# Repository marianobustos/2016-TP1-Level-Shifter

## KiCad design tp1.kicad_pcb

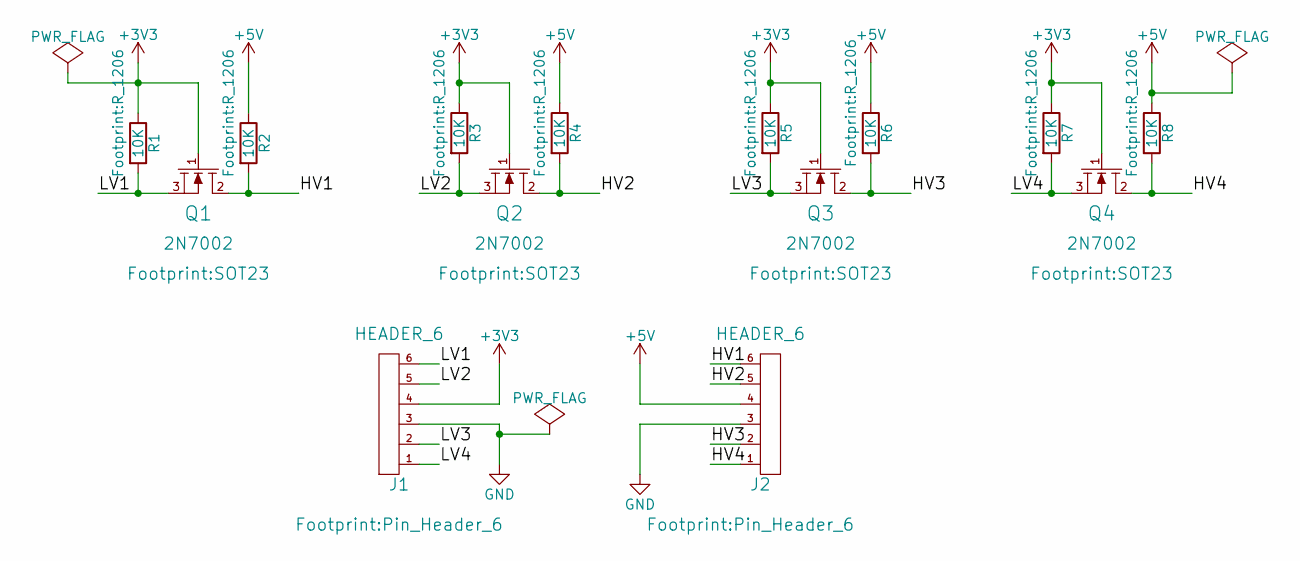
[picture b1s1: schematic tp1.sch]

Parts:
J1, J2: HEADER_6; Pin_Header_6
Q1, Q2, Q3, Q4: 2N7002; SOT23
R1, R2, R3, R4, R5, R6, R7, R8: 10K; R_1206

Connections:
+3V3: J1.4, Q1.1 (G), Q2.1 (G), Q3.1 (G), Q4.1 (G), R1.1, R3.1, R5.1, R7.1
+5V: J2.4, R2.1, R4.1, R6.1, R8.1
/HV1: J2.6, Q1.2 (D), R2.2
/HV2: J2.5, Q2.2 (D), R4.2
/HV3: J2.2, Q3.2 (D), R6.2
/HV4: J2.1, Q4.2 (D), R8.2
/LV1: J1.6, Q1.3 (S), R1.2
/LV2: J1.5, Q2.3 (S), R3.2
/LV3: J1.2, Q3.3 (S), R5.2
/LV4: J1.1, Q4.3 (S), R7.2
GND: J1.3, J2.3

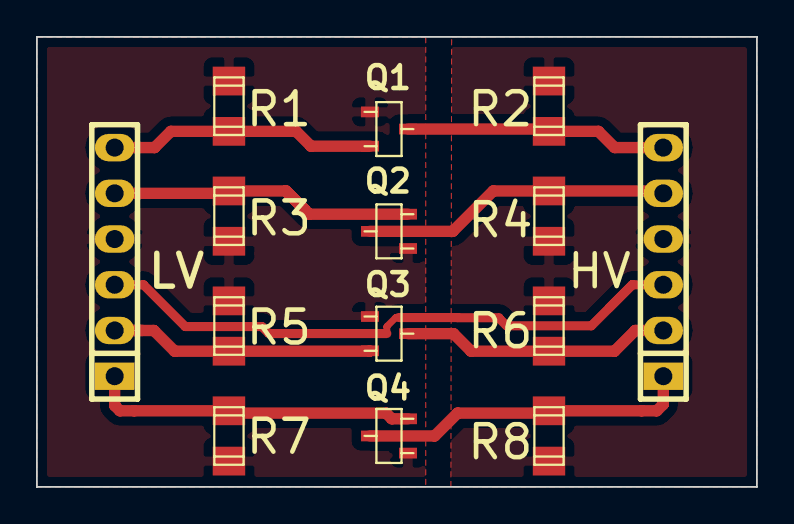
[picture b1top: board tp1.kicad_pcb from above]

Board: 2 copper layers, 40.0 x 25.0 mm, 14 parts (0 on the bottom side), 11 nets.

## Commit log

2017-01-10 :boom::camel: Added .gitattributes & .gitignore files
2017-01-10 Versión inicial TP1 2016
    TP1 del año 2016 de la materia "Diseño y Simulación Electrónica" del 5to
    año Electrónica de la E.E.S.T. N°5 de Temperley - Provincia de Buenos
    Aires. El TP fue diseñado por el Alumno Ignacio Vetrano.
